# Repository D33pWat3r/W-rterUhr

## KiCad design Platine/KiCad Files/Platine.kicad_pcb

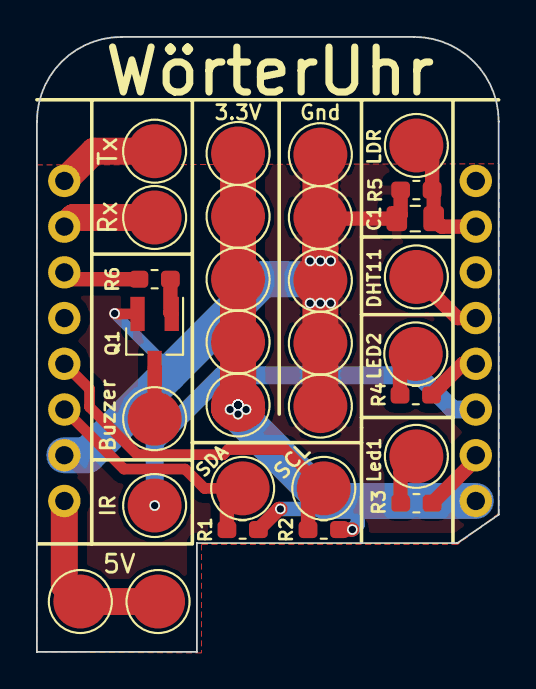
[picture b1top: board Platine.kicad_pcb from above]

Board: 2 copper layers, 25.7 x 34.2 mm, 31 parts (1 on the bottom side), 17 nets.

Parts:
C1: 1µ; C_0805_2012Metric_Pad1.15x1.40mm_HandSolder
J1, J17: 5V; TestPoint_Pad_D3.0mm
J2, J8, J10, J14, J22: Gnd; TestPoint_Pad_D3.0mm
J3: Led1; TestPoint_Pad_D3.0mm
J4, J5, J11, J15, J19: 3.3V; TestPoint_Pad_D3.0mm
J6: IR; TestPoint_Pad_D3.0mm
J7: SDA; TestPoint_Pad_D3.0mm
J9: SCL; TestPoint_Pad_D3.0mm
J12: LED2; TestPoint_Pad_D3.0mm
J13: DHT11; TestPoint_Pad_D3.0mm
J16: LDR; TestPoint_Pad_D3.0mm
J18: Buzzer; TestPoint_Pad_D3.0mm
J20: Rx; TestPoint_Pad_D3.0mm
J21: Tx; TestPoint_Pad_D3.0mm
Q1: S8050; SOT-23_Handsoldering
R1: 10k; R_0603_1608Metric_Pad1.05x0.95mm_HandSolder
R2: 10; R_0603_1608Metric_Pad1.05x0.95mm_HandSolder
R3, R4: 220; R_0603_1608Metric_Pad1.05x0.95mm_HandSolder
R5: 20k; R_0603_1608Metric_Pad1.05x0.95mm_HandSolder
R6: 1k; R_0603_1608Metric_Pad1.05x0.95mm_HandSolder
U1: WeMos_mini; wemos-d1-mini-connectors-only

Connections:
+3V3: J4.1, J5.1, J11.1, J15.1, J19.1, R1.1, R2.1, U1.16
+5V: J1.1, J17.1, U1.1
GND: C1.2, J2.1, J8.1, J10.1, J14.1, J22.1, Q1.2, R5.2, U1.2
unnamed: C1.1, J16.1, R5.1, U1.10
unnamed: J3.1, R3.1
unnamed: J6.1, U1.14
unnamed: J7.1, R1.2, U1.3
unnamed: J9.1, R2.2, U1.4
unnamed: J12.1, R4.2
unnamed: J13.1, U1.12
unnamed: J18.1, Q1.3
unnamed: J20.1, U1.7
unnamed: J21.1, U1.8
unnamed: Q1.1, R6.1
unnamed: R3.2, U1.15
unnamed: R4.1, U1.13
unnamed: R6.2, U1.6

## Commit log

2018-12-11 KiCad Files for circuit
2018-12-11 move picture files to a seperate folder
2018-12-11 pictures of the curcuits
2018-12-11 new pictures
2018-12-11 move KiCad Files to other folder
